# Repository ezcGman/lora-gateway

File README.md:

# LoRa-To-MQTT Gateway
## Introduction
This repository gives you everything you need to easily build (it's a DIY project!) a great quality LoRa-To-MQTT gateway, based on EByte LoRa modules and an ESP32 and works either with Wi-Fi or Ethernet, running off 5V. There are two different versions of the gateway, details on those versions and which you should pick down below:
- One using an EByte E32
- One using an EByte E220

For giving the board Ethernet capability, I'm using the [QuinLED ESP32 Ethernet Hat](https://quinled.info/quinled-esp32-ethernet/). Of course, It's natural that I *should* have also used a [QuinLed ESP32](https://quinled.info/quinled-esp32/), but I had a few spare standard ESP32 devboards laying around with no use for, so I designed the board around these. But that said, I might one day design a version completely based on the QuinLED-ESP32.

To easily switch between Wi-FI and Ethernet, there's a jumper on the board to do just that. This even works with the board powered; no need to cut power.

## What do I need to do to get one?
Again, this is a DIY project! So first off, you need a few soldering skills and I highly recommend either a SMD hot plate or hot air gun to solder the Ebyte E32 module. Its **very very hard** to solder it with just an iron!

### 1. Get the PCBs
So you want to get the PCBs printed at a PCB prototype factory of your choice, like JLCPCB or PCBWay. I've included the Gerber files for both in the respectiv folder. If you want to use a different service provider, you need to check if they may accept these gerbers or generate them yourself.

I also **highly recommend** that you order this PCB with a stencil, otherwise you gonna have a hard time putting the paste on the pads of the EByte module!

### 2. Get the components
* Look up the iBOM files to get a list of components you need:
    * [E32 version iBOM](https://github.com/ezcGman/lora-gateway/blob/master/pcbs/LoRa-Gateway-E32/ibom/LoRa-Gateway-E32.html)
    * [E220 version iBOM](https://github.com/ezcGman/lora-gateway/blob/master/pcbs/LoRa-Gateway-E220/ibom/LoRa-Gateway-E220.html)
* Additional links for the ESP32 and QuinLED Ethernet hat:
    * Regular ESP 32 DevKit (pick one with 2x15 pins!!): https://www.aliexpress.com/wholesale?catId=0&initiative_id=SB_20220311122647&SearchText=esp32+devkit
    * *(optional, if you want Ethernet)* QuinLED ESP32 with Ethernet hat:
        * Worldwide store: https://shop.allnetchina.cn/collections/quinled/products/quinled-esp32
        * US only: https://drzzs.com/shop/quinled-esp32/

### 3. Build the board and wire it up
Each PCB folder has an iBOM HTML file which gives you nice soldering instructions / overview, find it in the `ibom` folder in each versions folder. When you've soldered the board, simply wire it up with a 5V power source and there you go! It consumes less than 200mA, so you can easily use an old 500mA, 1A (or higher) phone charger for it.

### 4. Install the software
Source is available in the `src` folder. Download Arduino IDE, check the `config.h` file and replace the placeholders with your settings, compile and upload to the ESP32. That should be it and the gateway should pop up in your MQTT server and send health check messages every 5 seconds.

How you can now have your sensors and boards have LoRa messages sent to it can be found in the ["Source Code / Software"](#source-code--software) section below.

## PCBs
### General design
- Can either be operated using Wi-Fi or Ethernet
    - Jumper on board to (even with powered-on board) switch between those two
- Uses a standard **30-pin (2x15-pin)** ESP32 DevKit
- For Ethernet, uses the [QuinLED ESP32 Ethernet Hat](https://quinled.info/quinled-esp32-ethernet/)
- Easily powered using a screw terminal
- Extra protection using a PTC fuse, in case something goes sideways
- *Can* also be powered via USB on the ESP32, but this will skip the PTC fuse and with that your protection. So **not recommended**
- Four M2.5 mounting holes to mount it to or into whatever you want

Which one should you pick? That's pretty easy and defined by one factor:
- If you / your sensors and other boards use the RFM95 modules and the Arduino-LoRa library: Use the E32 version!
- If you usually use EByte modules that use serial communication and Renzo Mischiantis [famous Arduino library](https://github.com/xreef/LoRa_E32_Series_Library): Use the E220 version.

You need to choose between those, as the EByte modules that use serial communication can't communicate with the RFM95 modules, although they use the same Semtech SX1276 LoRa chip. That's because the EByte serial-operated modules also have a litte MCU onboard that already does its own "stuff" / protocol when sending messages via LoRa. So you don't talk directly to the Semtech chip, but that little MCU instead. One would need to understand how exactly that works to read these messages with a LoRa modules that uses direct SPI communication to the Semtech chip (like the specific E32 module I use, or the RFM95) to make them work with each other.

### LoRa-Gateway-E32

This version is based on the EByte E32-400M20S or E32-900M20S, which offers direct serial communicaton to the Semtech SX1276. At the time of last research (begin of 2022), this is the only E-Byte module that works on this PCB, so you can't use any other that uses serial communication: They won't fit on the board / have a different pinout! Pick the right one for your region (tl;dr: 400 for US/Asia, 900 for Europe).

The module is **not** in the BOM CSV file, you need to get it off AliExpress:
- 400MHz:
    - EBYTE IOT Factory Store: https://www.aliexpress.com/item/1005003567891629.html
    - cojxu Official Store: https://www.aliexpress.com/item/1005003567929089.html
- 900MHz
    - EBYTE IOT Factory Store: https://www.aliexpress.com/item/1005003509312425.html
    - cojxu Official Store: https://www.aliexpress.com/item/1005003646639064.html

### LoRa-Gateway-E220

If you usually work in the EByte ecosystem with its serial interfaced modules, this board is for you. **However** I've not done a port of my E32 based software for this board. And I'm actually not planning to do so, as I personally use the E32 version. But you're welcome to port it using Renzo Mischiantis [Arduino library](https://github.com/xreef/LoRa_E32_Series_Library).

The module is **not** in the BOM CSV file, you need to get it off AliExpress:
- 400MHz:
    - EBYTE IOT Factory Store: https://www.aliexpress.com/item/1005002090403425.html
    - cojxu Official Store: https://www.aliexpress.com/item/1005002060190690.html
- 900MHz
    - EBYTE IOT Factory Store: https://www.aliexpress.com/item/1005002116885160.html
    - cojxu Official Store: https://www.aliexpress.com/item/1005003681666059.html

## Source Code / Software
The software I've developed for this is meant to be easily extensible without touching the actual logic of the gateway itself, but instead adding a little piece of code to a separate file.

Take a look at [`lora-ids.h`](/src/lora-gateway-e32/lora-ids.h). This file is meant to be shared between this gateway and all sensors you develop. It has a list of different message types and you can easily add your own. E.g., it has a "mailbox" type which defines a few properties a mailbox would send. This makes it very easy to read and process this messages **and** create topics in your MQTT server which you then can listen to. There's also a "custom" type which basically has free text and is maybe good for debugging. 

Feel free to add your own types in this file. You will need to add two things:
* An ID for it, like `#define LORA_MESSAGE_ID_CUSTOM 0x0`
* Define the struct that describes its properties: `struct LoRaMessageCustom : LoRaBase`

### How do the MQTT topics look like I can subscribe to?
The subject where a message falls into is built out of the gateway ID, device ID and message ID. So for the following example we assume that:
* Device with ID `0xA` and name `mailbox-sensor` has sent
* a message of type `LORA_MESSAGE_ID_MAILBOX` and
* the gateway with ID `0x1` and name `lora-gateway-e32` receives it.

So let's first take the `mailbox` message type as an example. It define these properties:
* long duration
* float distance
* float humidity
* float temperature

Additionally, it defines its own name (and with that: The parent for these properties):
* `String getMqttTopicName() { return "mailbox"; }`

So whenever the gateway will receive a message of this type, it will read the properties from it and drop them into these topics:
* `???/messages/mailbox/duration`
* `???/messages/mailbox/distance`
* `???/messages/mailbox/humidity`
* `???/messages/mailbox/temperature`

But where does the `/messages/` part come form and what is `???/`. That's easy: Easy device / sensor you develop should also be registered in `lora-ids.h`. At the very top, there is list of devices, each with:
* Device ID
* Device name (which affectively is used to construct the MQTT topic)

The gateway will sort all messages it receives by device and prefixes it with that device name, *plus* sorts all messages under a `messages` topic to allow the device have other topics next to the actual messages. This allows you to listen to specific fields/values of specific message types from a specific device!

So we now know this:
* `???/mailbox-sensor/messages/mailbox/duration`
* `???/mailbox-sensor/messages/mailbox/distance`
* `???/mailbox-sensor/messages/mailbox/humidity`
* `???/mailbox-sensor/messages/mailbox/temperature`

The last missing piece is the gateway that receives the messages. It's also defined as a device, so it also has a name, so we can easily construct the full topic name for our example:
* `lora-gateway-e32/devices/mailbox-sensor/messages/mailbox/duration`
* `lora-gateway-e32/devices/mailbox-sensor/messages/mailbox/distance`
* `lora-gateway-e32/devices/mailbox-sensor/messages/mailbox/humidity`
* `lora-gateway-e32/devices/mailbox-sensor/messages/mailbox/temperature`

Now you can easily:
* Add your own devices by:
    * Adding it to the `LORA_DEVICE_IDS` with an ID and name
* Add new message types by:
    * Define an ID for it
    * Define the struct that describes it

### How can I actually send messages?
Take a look at the [`sendLoRaMessage`](/src/lora-gateway-e32/lora-ids.h#L160) function:
`bool sendLoRaMessage(byte messageID, LoRaBase *loRaMessage, byte recipientId = 0, byte senderId = 0)`
It expects us to give it:
* The message ID we're going to send
* As also the message itself

We can also optionally specify:
* The recipientId of this message. If not specified, it defaults to `LORA_GATEWAY_ID`
* The senderId, which defaults to `LORA_DEVICE_ID`, if not specified

So in your code, simply create an instance of the message ID you want to send and pass it to `sendLoRaMessage`:
```
LoRaMessageMailbox *loRaMessage = new LoRaMessageMailbox;
loRaMessage->duration = duration;
loRaMessage->distance = distance;
loRaMessage->humidity = humidity;
loRaMessage->temperature = temperature;

sendLoRaMessage(LORA_MESSAGE_ID_MAILBOX, loRaMessage);
```
And that's it :)

#### How does it work under the hood?
For this we take a look at how the actual message is constructed that is sent via LoRa. The *basic idea* is stolen from the Arduino-LoRa library, which uses singly bytes to identify senders, receivers, etc.

Looking at a single message:
* 1st byte is the recipient ID
    * This can also be set to 0xFF, which indicates a broadcase message that is received and can be processed by all devices.
* 2nd byte is the sender ID
* 3rd byte is the message ID
* 4th-255th byte is the message we will split up
    * The message simply has all values joined together by a `|`. So taking the `mailbox` message example from above, the value for the message could look like this: `12345|3.56|44.55|27.4`

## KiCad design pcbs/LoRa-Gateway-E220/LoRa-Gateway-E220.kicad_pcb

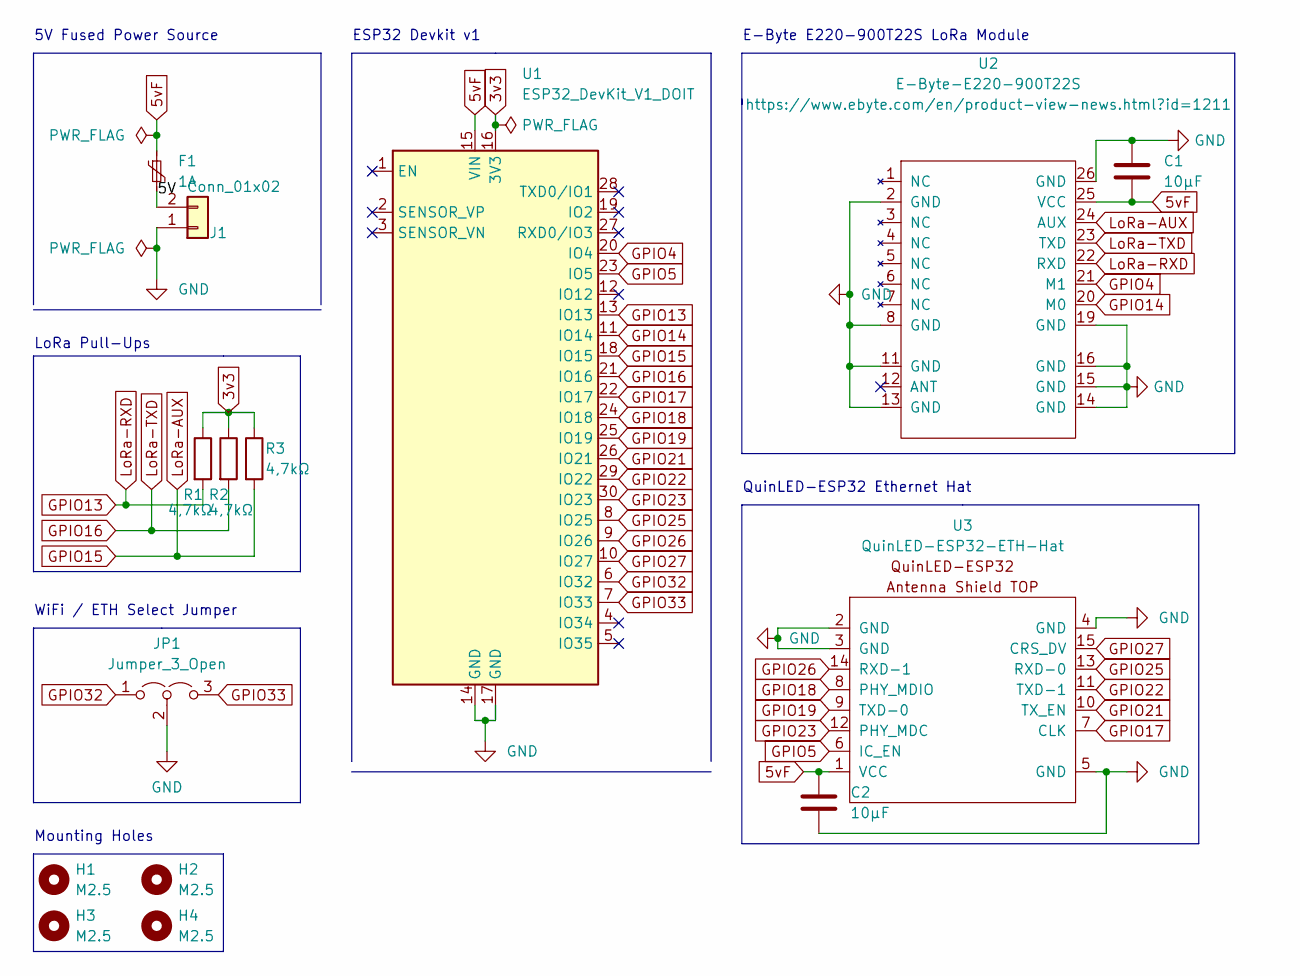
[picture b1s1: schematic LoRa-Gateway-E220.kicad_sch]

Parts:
C1, C2: 10µF; C_0805_2012Metric
F1: 1A; Fuse_1812_4532Metric
H1, H2, H3, H4: M2.5; MountingHole_2.5mm_Pad_Via
J1: Conn_01x02; TerminalBlock_Phoenix_MKDS-1,5-2-5.08_1x02_P5.08mm_Horizont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
JP1: Jumper_3_Open; PinHeader_1x03_P2.54mm_Vertical
R1, R2, R3: 4,7kΩ; R_0805_2012Metric
U1: ESP32_DevKit_V1_DOIT; esp32_devkit_v1_doit-less-silkscreen
U2: E-Byte-E220-900T22S; E-Byte-E220-xxxT22S
U3: QuinLED-ESP32-ETH-Hat

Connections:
3v3: R1.1, R2.1, R3.1, U1.16 (3V3)
5vF: C1.2, C2.1, F1.1, U1.15 (VIN), U2.25 (VCC), U3.1 (VCC)
/5V: F1.2, J1.2
GND: C1.1, C2.2, J1.1, JP1.2 (C), U1.14 (GND), U1.17 (GND), U2.2 (GND), U2.8 (GND), U2.11 (GND), U2.13 (GND), U2.14 (GND), U2.15 (GND), U2.16 (GND), U2.19 (GND), U2.26 (GND), U3.2 (GND), U3.3 (GND), U3.4 (GND), U3.5 (GND)
GPIO4: U1.20 (IO4), U2.21 (M1)
GPIO5: U1.23 (IO5), U3.6 (IC_EN)
GPIO13: R1.2, U1.13 (IO13), U2.22 (RXD)
GPIO14: U1.11 (IO14), U2.20 (M0)
GPIO15: R3.2, U1.18 (IO15), U2.24 (AUX)
GPIO16: R2.2, U1.21 (IO16), U2.23 (TXD)
GPIO17: U1.22 (IO17), U3.7 (CLK)
GPIO18: U1.24 (IO18), U3.8 (PHY_MDIO)
GPIO19: U1.25 (IO19), U3.9 (TXD-0)
GPIO21: U1.26 (IO21), U3.10 (TX_EN)
GPIO22: U1.29 (IO22), U3.11 (TXD-1)
GPIO23: U1.30 (IO23), U3.12 (PHY_MDC)
GPIO25: U1.8 (IO25), U3.13 (RXD-0)
GPIO26: U1.9 (IO26), U3.14 (RXD-1)
GPIO27: U1.10 (IO27), U3.15 (CRS_DV)
GPIO32: JP1.1 (A), U1.6 (IO32)
GPIO33: JP1.3 (B), U1.7 (IO33)

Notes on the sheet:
QuinLED-ESP32 Ethernet Hat
WiFi / ETH Select Jumper
5V Fused Power Source
LoRa Pull-Ups
Mounting Holes
E-Byte E220-900T22S LoRa Module
ESP32 Devkit v1

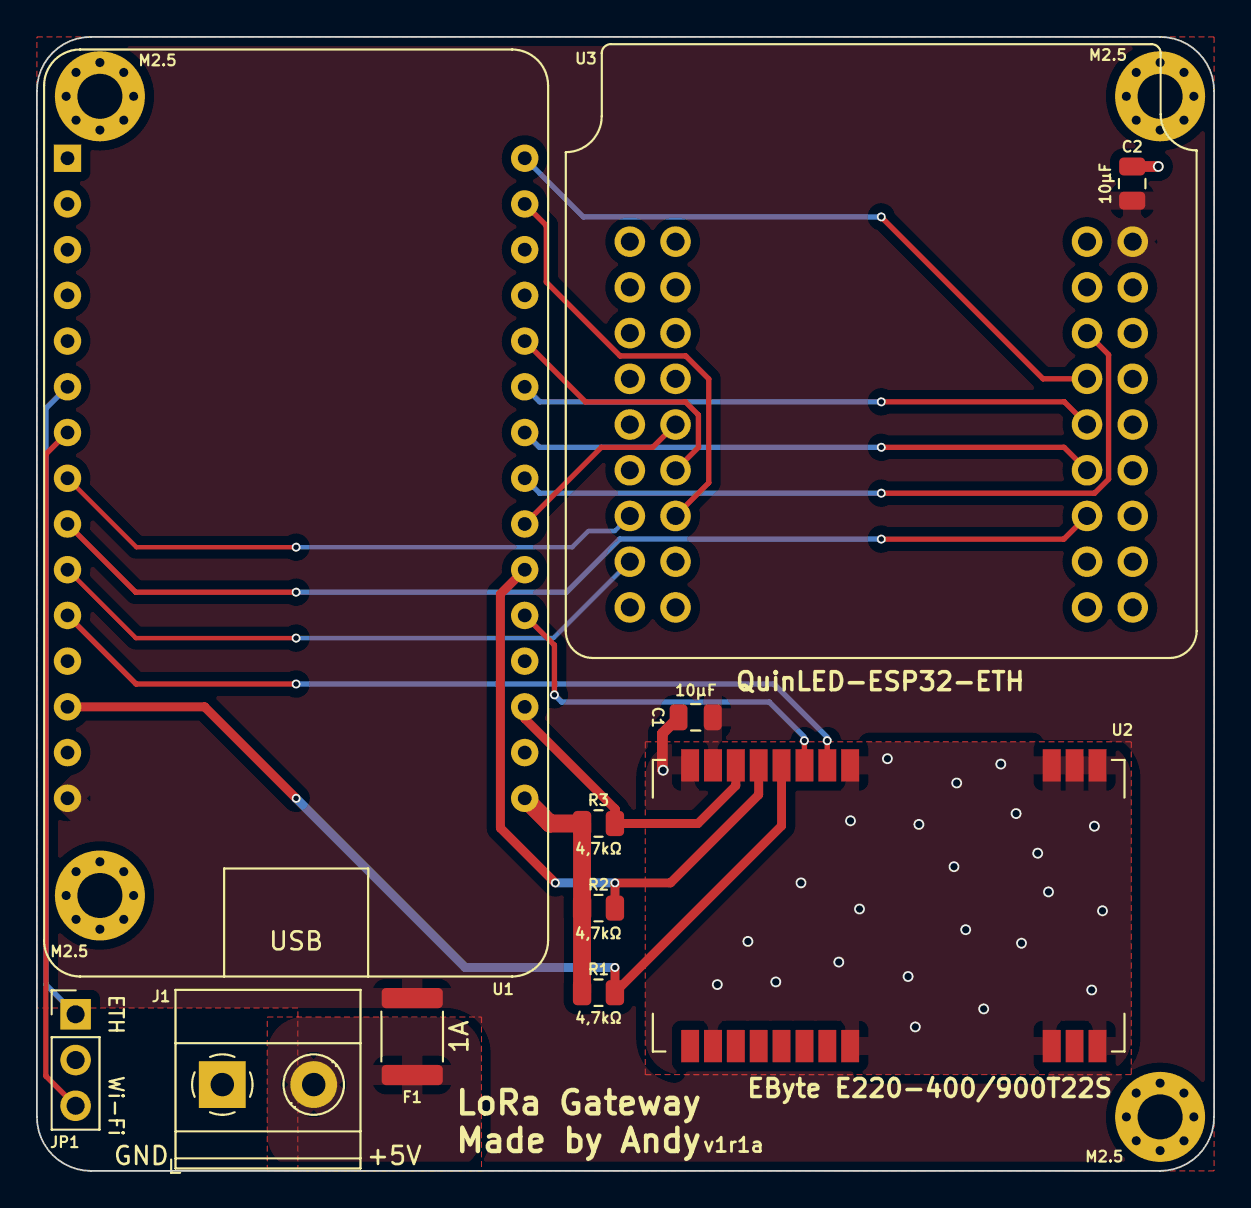
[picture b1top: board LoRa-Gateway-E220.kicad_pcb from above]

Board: 2 copper layers, 65.4 x 63.0 mm, 15 parts (0 on the bottom side), 21 nets.

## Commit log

2022-03-04 Added first public version of my gateway PCBs
2022-03-10 First version of the Ebyte-E32 LoRa-Gateway software
2022-03-11 Added iBOM, last small edits on both PCBs
2022-09-27 Added support for washing machine sensor
2022-09-27 Added gerbers for both boards and both JLCPCB and PCBWay
2022-09-28 Added new sendLoRaMessage function
2022-10-03 Added uptime and status MQTT topics
